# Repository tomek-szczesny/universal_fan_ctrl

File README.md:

# universal_fan_ctrl

An autonomous, temperature dependent fan controller

The aim of the project is to develop a fan controller module that can be applied to fans in existing appliances that otherwise have no speed control. The module is intended to be connected as a pass-through between the fan and its original power source.

## Features

- 4.5V - 30V input voltage range
- Low side 1A PWM switch controls any DC fan, with of without PWM pin
- 11.6 x 13.6 mm 2-layer PCB, no bottom side components
- Cheap BOM with hand-solderable 0603 passives
- BOM-configurable parameters
- 2.54mm pitch input and output THT pads for wires or connectors
- On-board or remote temperature sensor (DS18B20), or AVR internal sensor

## Operation

- PWM fixed at 100Hz
- In absence of DS18B20 temperature sensor, falls back to the internal AVR sensor
- Temperature probed at 5Hz
- Digital low pass filters reduce measurement noise
- Configurable Maximum temperature (MT) and Temperature ramp length (TR)
  -   Fan stays off at T < (MT-TR)
  -   Fan's PWM is mapped to (23.2% - 100%) range within (MT-TR) < T < MT range
  -   Fan stays fully on at T > MT

## Configuration

The microcontroller senses two ADC values on startup, which determine mode of operation. They can be easily changed by replacing two resistors on board.

### Maximum temperature (MT)

The temperature at which the fan works at the maximum speed. Resistor Rmt controls this parameter.

| Max Temperature | Rmt value  |
| --------------- | ---------- |
| 30C             | Open       |
| 35C             | 68k        |
| 40C             | 33k        |
| 45C             | 20k        |
| 50C             | 12k        |
| 55C             | 6k8        |
| 60C             | 3k6        |
| 65C             | 1k or less |

### Ramp length (TR)

The temperature range that is mapped linearly to 23.2% - 100% PWM output This parameter is controlled by resistor Rtr.

| Ramp Length | Rtr value   |
| ----------- | ----------- |
| 2.5C        | Open        |
| 5C          | 33k         |
| 10C         | 12k         |
| 20C         | 2k7 or less |

## Schematic

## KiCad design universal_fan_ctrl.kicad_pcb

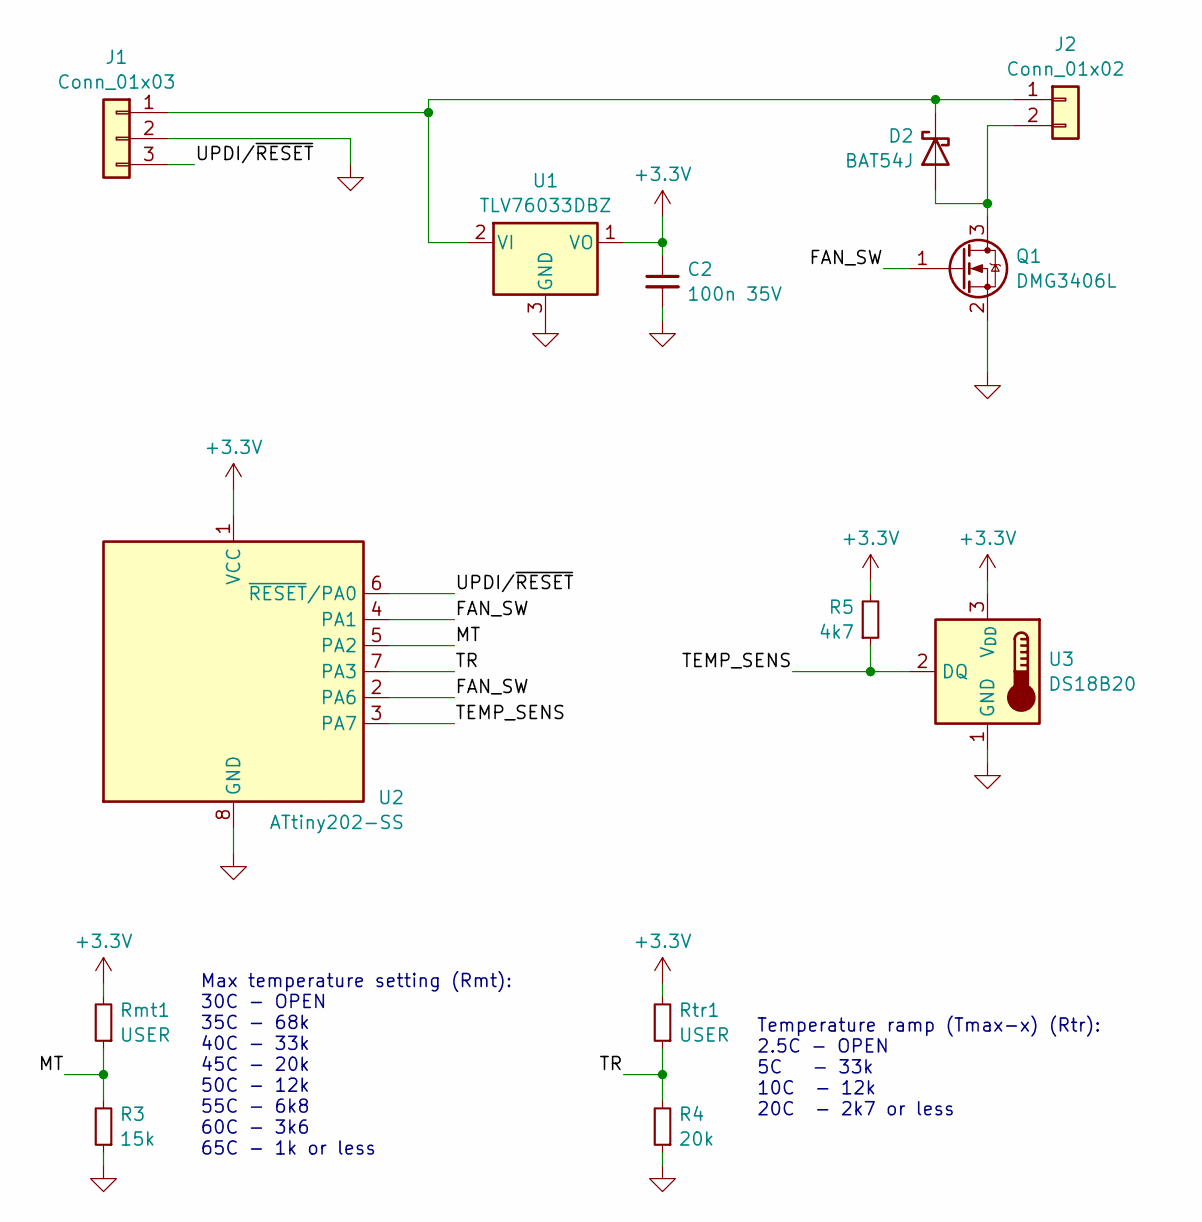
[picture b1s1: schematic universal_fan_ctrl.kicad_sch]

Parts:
C2: 100n 35V; R_0603_1608Metric; LCSC C14663
D2: BAT54J; D_SOD-323F
J1: Conn_01x03; PinHeader_1x03_P2.54mm_Vertical
J2: Conn_01x02; PinHeader_1x02_P2.54mm_Vertical
Q1: DMG3406L; SOT-23; LCSC C460978
R3: 15k; R_0603_1608Metric; LCSC C22809
R4: 20k; R_0603_1608Metric; LCSC C4184
R5: 4k7; R_0603_1608Metric; LCSC C23162
Rmt1: USER; R_0603_1608Metric; LCSC C4184
Rtr1: USER; R_0603_1608Metric; LCSC C22790
U1: TLV76033DBZ; SOT-23; LCSC C2683368
U2: ATtiny202-SS; SOIC-8_3.9x4.9mm_P1.27mm; LCSC C2052951
U3: DS18B20; TO-92_Inline

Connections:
+3.3V: C2.1, R5.2, Rmt1.2, Rtr1.2, U1.1 (VO), U2.1 (VCC), U3.3 (V_{DD})
/FAN_SW: Q1.1 (G), U2.2 (PA6), U2.4 (PA1)
/MT: R3.2, Rmt1.1, U2.5 (PA2)
/TEMP_SENS: R5.1, U2.3 (PA7), U3.2 (DQ)
/TR: R4.2, Rtr1.1, U2.7 (PA3)
/UPDI/~RESET: J1.3, U2.6 (~RESET/PA0)
GND: C2.2, J1.2, Q1.2 (S), R3.1, R4.1, U1.3 (GND), U2.8 (GND), U3.1 (GND)
unnamed: D2.2 (A), J2.2, Q1.3 (D)
unnamed: D2.1 (K), J1.1, J2.1, U1.2 (VI)

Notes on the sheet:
Temperature ramp (Tmax-x) (Rtr): 2.5C - OPEN 5C - 33k 10C - 12k 20C - 2k7 or less
Max temperature setting (Rmt): 30C - OPEN 35C - 68k 40C - 33k 45C - 20k 50C - 12k 55C - 6k8 60C - 3k6 65C - 1k or less

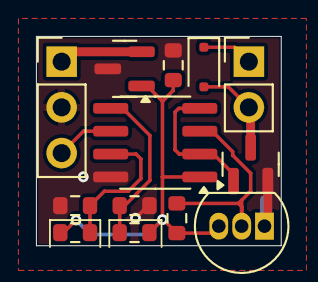
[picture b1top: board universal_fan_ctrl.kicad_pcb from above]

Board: 2 copper layers, 13.6 x 11.6 mm, 13 parts (0 on the bottom side), 9 nets.

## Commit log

2025-02-01 Initial commit - Hardware ready
2025-02-02 Schematic clean-up
2025-02-03 A stub of firmware
2025-02-04 FW progress
2025-02-05 Connected FAN_CTRL net to the spare AVR pin
2025-02-05 FW development
2025-02-13 Converted the code to 312.5kHz operation
2025-02-14 Changing system clock to 1MHz
2025-02-14 PWM section complete
2025-02-14 Introduced Sleep mode; more shenanigans
2025-02-15 Code seemingly complete
2025-02-15 Code cleaned up, not tested at all
2025-02-15 kicad update, addressing #1
2025-02-15 README update
